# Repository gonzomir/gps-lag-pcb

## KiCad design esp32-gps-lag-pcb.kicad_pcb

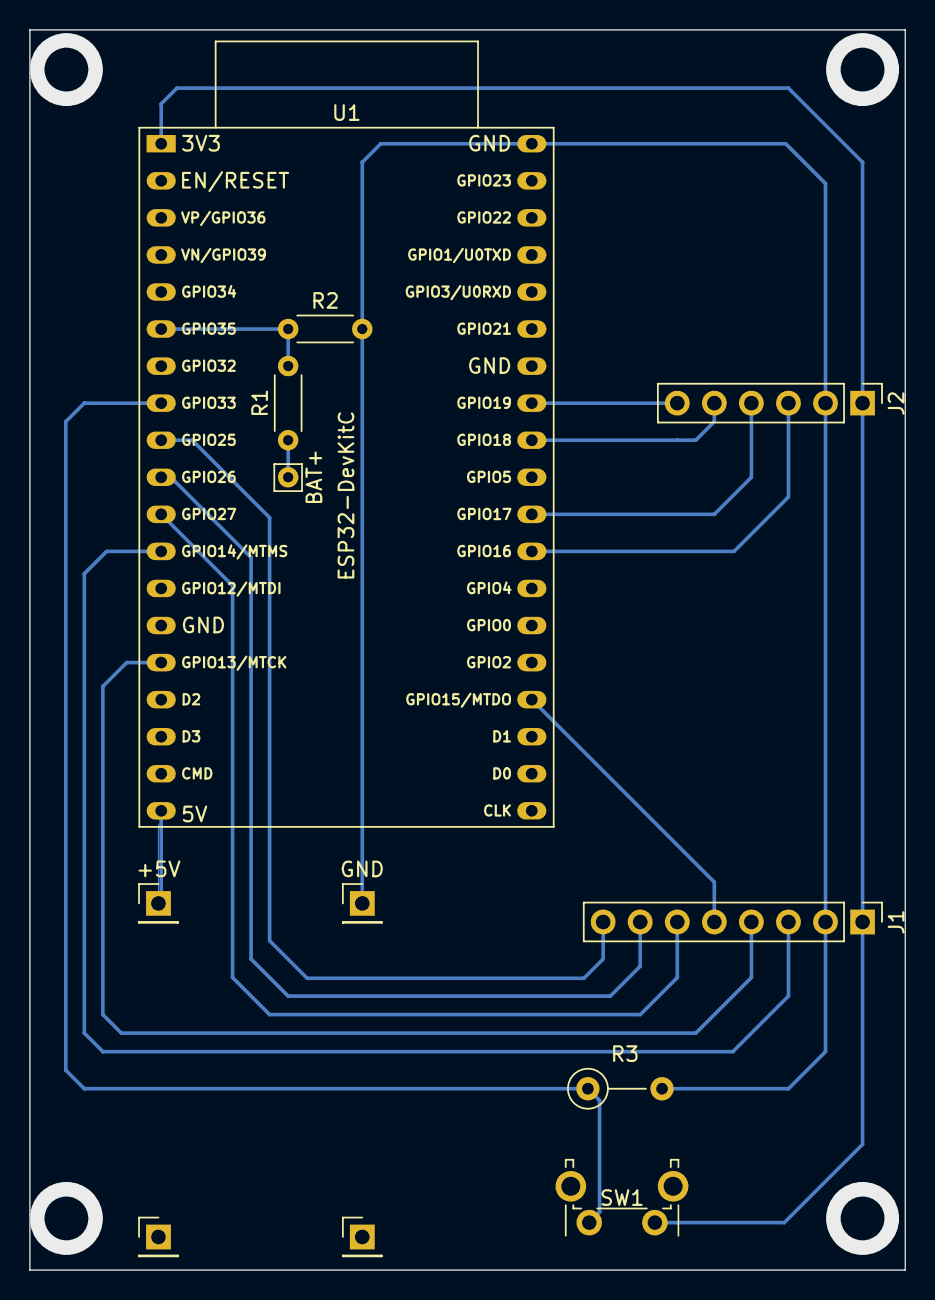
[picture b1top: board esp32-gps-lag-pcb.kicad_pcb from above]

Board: 2 copper layers, 60.0 x 85.0 mm, 10 parts (0 on the bottom side), 16 nets.

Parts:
+5V: PinHeader_1x01_P2.54mm_Vertical
BAT+: Pin_D0.7mm_L6.5mm_W1.8mm_FlatFork
GND: PinHeader_1x01_P2.54mm_Vertical
J1: eInk display; PinHeader_1x08_P2.54mm_Vertical
J2: GNSS; PinHeader_1x06_P2.54mm_Vertical
R1, R2: 100K; R_Axial_DIN0204_L3.6mm_D1.6mm_P5.08mm_Horizontal
R3: 10k; R_Axial_DIN0207_L6.3mm_D2.5mm_P5.08mm_Vertical
SW1: SW_Push; SW_Tactile_SPST_Angled_PTS645Vx39-2LFS
U1: ESP32-DevKitC

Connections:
+3.3V: J1.1, J2.1, SW1.2 (1), U1.1 (3V3)
+4V: BAT+.1, R1.1
+5V: +5V.1, U1.19 (5V)
GND: GND.1, J1.2, J2.2, R2.2, R3.2, U1.14 (GND), U1.32 (GND), U1.38 (GND)
unnamed: J1.3, U1.12 (MTMS/GPIO14/ADC2_CH6)
unnamed: J1.4, U1.15 (MTCK/GPIO13/ADC2_CH4)
unnamed: J1.5, U1.23 (MTDO/GPIO15/ADC2_CH3)
unnamed: J1.6, U1.11 (ADC2_CH7/GPIO27)
unnamed: J1.7, U1.10 (DAC_2/ADC2_CH9/GPIO26)
unnamed: J1.8, U1.9 (DAC_1/ADC2_CH8/GPIO25)
unnamed: J2.3, U1.27 (GPIO16)
unnamed: J2.4, U1.28 (GPIO17)
unnamed: J2.5, U1.30 (GPIO18)
unnamed: J2.6, U1.31 (GPIO19)
unnamed: R3.1, SW1.1 (2), U1.8 (32K_XN/GPIO33/ADC1_CH5)
unnamed: R1.2, R2.1, U1.6 (VDET_2/GPIO35/ADC1_CH7)

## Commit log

2024-01-09 Initial commit - first prototype PCB.
2024-01-09 Add .gitignore file.
2024-02-10 Battery capacity measurement, new GNSS module, etc.
2024-03-24 Change button and resistor footprints.
2024-03-24 Add PDFs of PCB and schematics.
